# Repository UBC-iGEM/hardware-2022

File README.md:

# hardware-2022
Arduino-based fluorometer device for the [UBC Vancouver iGEM 2022 project](https://2022.igem.wiki/ubc-vancouver/model).

- __"CAD stl"__ > The 3D printing design and manufacturing files can be found in this folder.
- __"elec"__ > The electrical circuit schematics and 3D model renders can be found in this folder.

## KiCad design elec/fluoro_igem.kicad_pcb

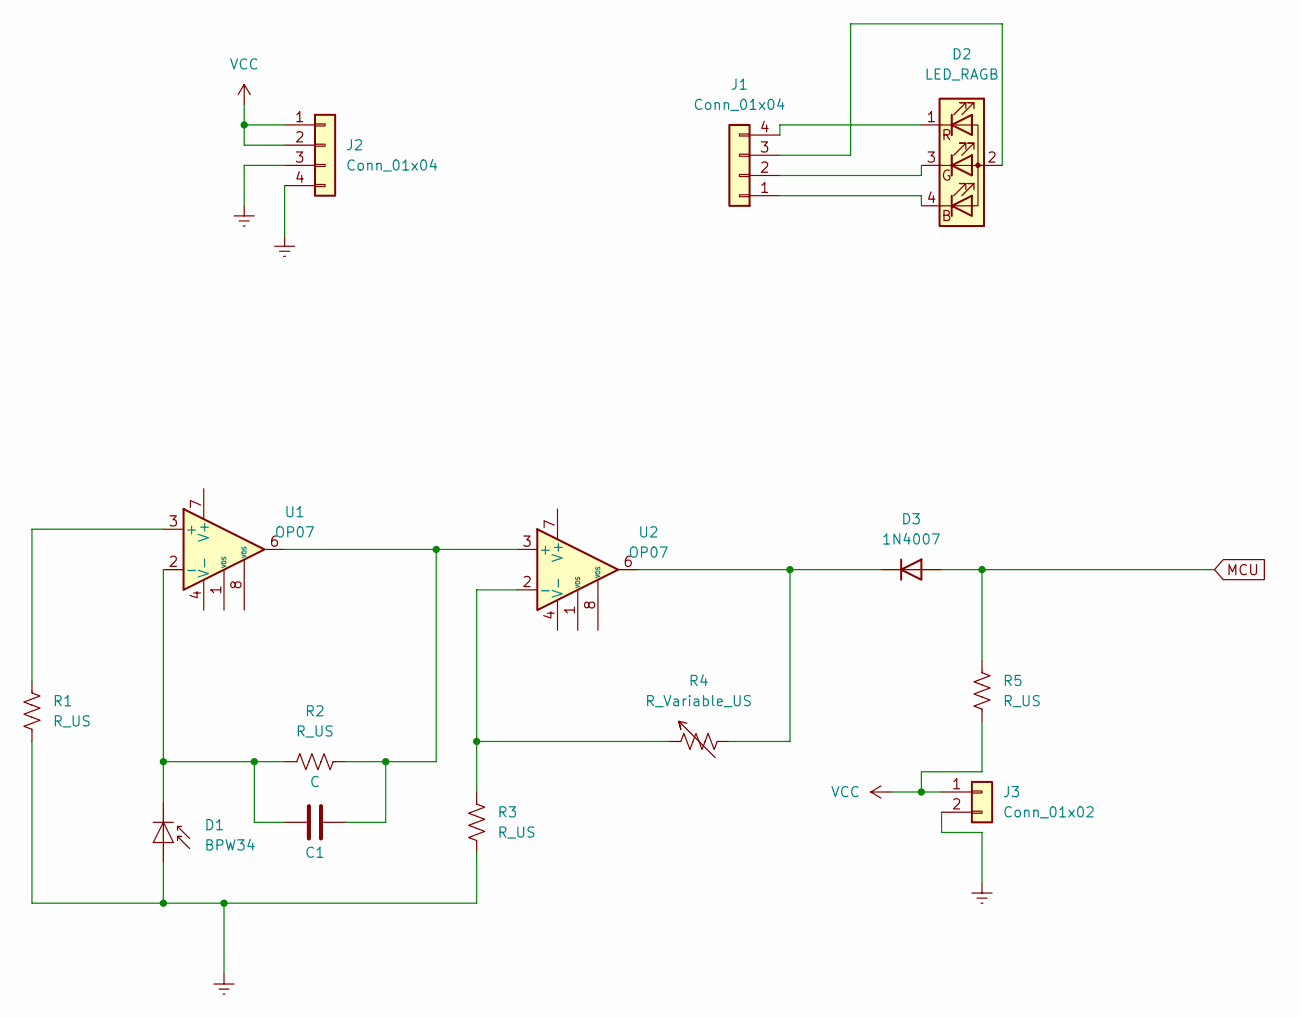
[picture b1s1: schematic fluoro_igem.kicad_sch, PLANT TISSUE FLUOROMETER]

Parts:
C1: C; CP_Radial_D4.0mm_P2.00mm
D1: BPW34; Osram_DIL2_4.3x4.65mm_P5.08mm
D2: LED_RAGB; LED_D5.0mm-4_RGB_Wide_Pins
D3: 1N4007; D_DO-41_SOD81_P10.16mm_Horizontal
J1, J2: Conn_01x04; FanPinHeader_1x04_P2.54mm_Vertical
J3: Conn_01x02; Molex_KK-254_AE-6410-02A_1x02_P2.54mm_Vertical
R1, R2, R3, R5: R_US; R_Axial_DIN0309_L9.0mm_D3.2mm_P2.54mm_Vertical
R4: R_Variable_US; Potentiometer_TT_P0915N
U1, U2: OP07; DIP-8_W7.62mm

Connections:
Earth: D1.2 (A), J2.3, J2.4, J3.2, R1.1, R3.1
MCU: D3.2 (A), R5.1
unnamed: C1.2, R2.2, U1.6, U2.3 (+)
unnamed: D3.1 (K), R4.2, U2.6
unnamed: D2.4 (BK), J1.1
unnamed: D2.3 (GK), J1.2
unnamed: D2.2 (A), J1.3
unnamed: D2.1 (RK), J1.4
unnamed: R1.2, U1.3 (+)
unnamed: C1.1, D1.1 (K), R2.1, U1.2 (-)
unnamed: R3.2, R4.1, U2.2 (-)
VCC: J2.1, J2.2, J3.1, R5.2

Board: 2 copper layers, 15 parts (1 on the bottom side), 12 nets, no tracks yet.

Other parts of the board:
Ge: LOGO

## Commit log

2022-10-14 add electrical kicad files
2022-10-14 add iGEM 2022 wiki link
